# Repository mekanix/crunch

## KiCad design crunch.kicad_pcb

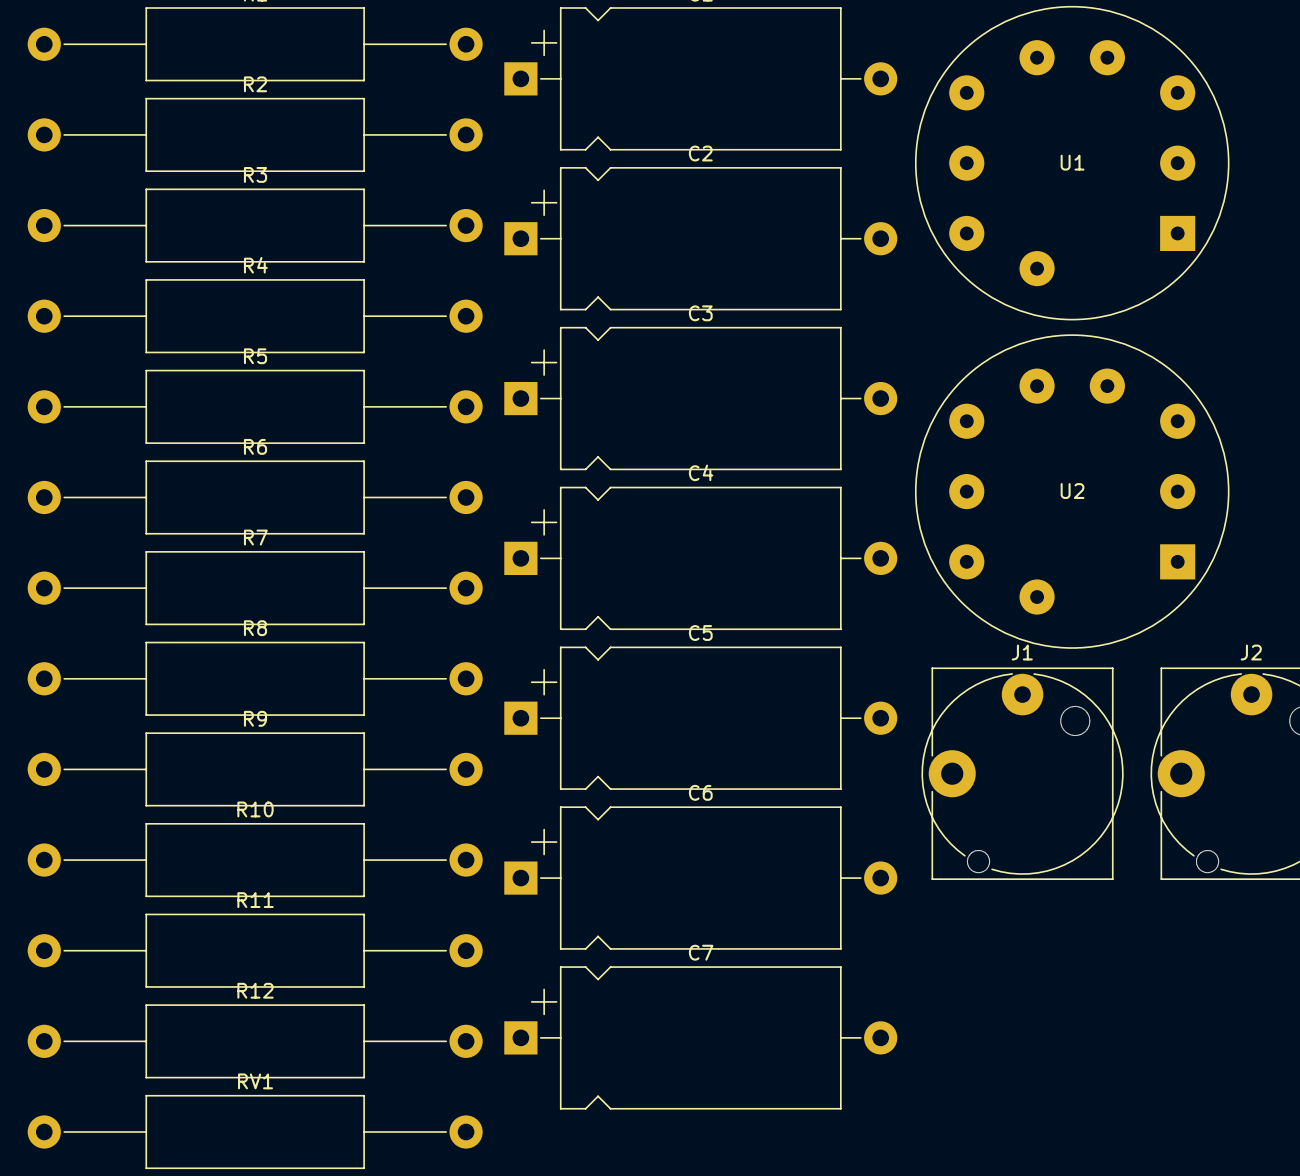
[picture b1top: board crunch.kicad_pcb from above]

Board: 2 copper layers, 24 parts (0 on the bottom side), 18 nets, no tracks yet.

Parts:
C1: 680n; CP_Axial_L20.0mm_D10.0mm_P26.00mm_Horizontal
C2, C5, C7: 22n; CP_Axial_L20.0mm_D10.0mm_P26.00mm_Horizontal
C3, C6: 470p/disk; CP_Axial_L20.0mm_D10.0mm_P26.00mm_Horizontal
C4: 1n/disk; CP_Axial_L20.0mm_D10.0mm_P26.00mm_Horizontal
J1, J2: AudioJack2; Jack_6.35mm_Neutrik_NJ2FD-V_Vertical
R1: 1M; R_Axial_DIN0516_L15.5mm_D5.0mm_P30.48mm_Horizontal
R2: 68k; R_Axial_DIN0516_L15.5mm_D5.0mm_P30.48mm_Horizontal
R3: 2k7; R_Axial_DIN0516_L15.5mm_D5.0mm_P30.48mm_Horizontal
R4, R7, R11, R12: 100k; R_Axial_DIN0516_L15.5mm_D5.0mm_P30.48mm_Horizontal
R5, R8, R9: 470k; R_Axial_DIN0516_L15.5mm_D5.0mm_P30.48mm_Horizontal
R6: 10k; R_Axial_DIN0516_L15.5mm_D5.0mm_P30.48mm_Horizontal
R10: 820; R_Axial_DIN0516_L15.5mm_D5.0mm_P30.48mm_Horizontal
RV1: 1M/log; R_Axial_DIN0516_L15.5mm_D5.0mm_P30.48mm_Horizontal
U1, U2: ECC83; Valve_Noval_P

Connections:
Earth: C1.2, J1.T, J2.T, R1.2, R3.2, R6.2, R9.2, R10.2, R12.2
unnamed: C2.2, C3.1, R5.1
unnamed: C3.2, C4.1, R5.2, RV1.1
unnamed: C5.2, C6.1, R8.1
unnamed: C7.2, J2.S
unnamed: J1.S, R1.1, R2.1
unnamed: R4.1, R7.1
unnamed: C2.1, R4.2, U1.6 (A)
unnamed: R2.2, U1.7 (G)
unnamed: C1.1, R3.1, U1.8 (K)
unnamed: C5.1, R7.2, U1.1 (A)
unnamed: C4.2, RV1.2, U1.2 (G)
unnamed: R6.1, U1.3 (K)
unnamed: R11.2, U2.2 (G), U2.6 (A)
unnamed: C6.2, R8.2, R9.1, U2.7 (G)
unnamed: R10.1, U2.8 (K)
unnamed: R11.1, U2.1 (A)
unnamed: C7.1, R12.1, U2.3 (K)
